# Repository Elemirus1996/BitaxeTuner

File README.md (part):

<p align="center"></p>

<p align="center">
  <a href="https://github.com/Elemirus1996/BitaxeTuner/releases/latest"><b>⬇ Herunterladen</b></a> ·
  <a href="https://elemirus1996.github.io/BitaxeTuner/"><b>Webseite</b></a> ·
  <a href="https://elemirus1996.github.io/BitaxeTuner/pico-luefter/">Pico-Bauanleitung</a> ·
  <a href="#247-betrieb">24/7-Server</a> ·
  <a href="README.en.md"><b>English</b></a>
</p>

# BitaxeTuner

**Automatisches Übertakten, Benchmarken und Überwachen für Bitaxe- und NerdAxe-Miner – als Windows-Programm (WPF)
und als [24/7-Server](#247-betrieb) für Raspberry Pi, Windows oder Docker mit Browser-Oberfläche.**
*Automatic overclocking & benchmarking for Bitaxe and NerdAxe miners – [English README](README.en.md).*

BitaxeTuner erhöht Frequenz und Kernspannung deines Miners Schritt für Schritt, misst jede Kombination
(Hashrate, Leistung, Effizienz, Temperaturen, Fehlerrate) und zeigt dir am Ende die beste Einstellung –
wahlweise für **maximale Hashrate**, **beste Effizienz (J/TH)** oder einen **Kompromiss** aus beidem.
Mehrere Geräte lassen sich **parallel** testen.

> ⚠️ **Übertakten auf eigenes Risiko.** Höhere Frequenz und Spannung erhöhen Leistungsaufnahme und Temperatur
> und können die Hardware beschädigen. Prüfe, ob Netzteil und Kühlung ausreichen.

## Sprache

Desktop-App, Browser-Oberfläche, Push-Meldungen, Tagesbericht, E-Paper-Anzeige und Home Assistant gibt es auf
**Deutsch, Englisch, Spanisch, Portugiesisch (Brasilien), Französisch und Niederländisch** (ab 0.9.12; die vier
neuen Sprachen sind maschinell übersetzt – Verbesserungen von Muttersprachlern gern als Issue oder Pull Request):

- **Desktop-App**: *Einstellungen → Sprache* (Automatisch = Windows-Sprache), wirkt nach einem Neustart der App.
- **Browser**: Sprachauswahl im Kopf (DE, EN, ES, PT, FR, NL) – jeder Browser merkt sich seine Wahl (Standard: Browser-Sprache).
- **Server** (Push, Tagesbericht, E-Paper, Statustexte): *Einstellungen → Sprache des Servers* in der Browser-Oberfläche.
  Ein Raspberry Pi steht ab Werk auf Englisch – für deutsche Meldungen dort „Deutsch“ wählen.
- Zahlen und Datum folgen dem Format des Systems, solange dessen Sprache passt.

## Funktionen

### Tuning

- **Automatischer Benchmark** pro Gerät:
  stabil → Frequenz erhöhen · instabil → Spannung erhöhen · Grenze erreicht → sofort abbrechen.
  Optional wird pro Frequenz auch die niedrigste stabile Spannung gesucht (effizienter).
- **Sicherheits-Watchdog** bei jedem Messwert: max. Chip-Temperatur, VR-Temperatur, Leistung,
  Eingangsspannung, Überhitzungs- und Spannungsfehler der Firmware. Bei Abbruch, Fehler oder Programmende
  werden die ursprünglichen (oder die beste gefundene) Einstellungen wiederhergestellt.
- **Parallelbetrieb** mehrerer Miner, **Pause/Fortsetzen** und Fortsetzen abgebrochener Läufe.
- **Live-Ansicht** mit Hashrate-/Temperaturverlauf, **Heatmap** Frequenz × Spannung, Ergebnistabelle, CSV-Export.
  Ergebnisse per Klick auf die Spalten sortieren (z. B. J/TH aufsteigend) und direkt **in der Automatik speichern**
  (als Voreinstellung für Zeitplan und Strompreis – am Miner ändert sich dabei nichts).
- **Dauertest** und **Effizienz-Ratgeber** (siehe [Bedienung](#automatik-dauertest-vergleich-handy-ansicht)).
- **Simulationsmodus**: Adresse `sim` oder `sim:<profil-id>` eingeben (z. B. `sim:nerdqaxe-plusplus`) –
  zum Ausprobieren ohne echte Hardware (läuft 30× schneller).

### Überwachung

- **Gesamt- und Einzelansicht** mit 14 Kacheln, Wallet-Guthaben (mempool.space / Blockchair), Verlauf 1 h / 24 h /
  7 / 30 Tage aus `history.db` (Hashrate, Temperatur, Leistung, Effizienz J/TH).
- **Netzwerk**: zuletzt gefundene Blöcke, Pool-Ranking, Solo-Chancen BTC/BCH.
- **Gesundheits-Frühwarnung**: täglicher Vergleich der letzten 7 Tage mit den 4 Wochen davor – Kühlung (Temperatur je
  Watt), Effizienz ohne Tuning-Änderung, Lüfter-Drehzahl, abgelehnte Shares, Verfügbarkeit.
- **Watchdog** (Neustart bei 0 Hashrate; ab 0.9.12 auch, wenn die Hashrate eine einstellbare Zeit lang deutlich unter dem
  Normalwert liegt – Einstellungen → Überwachung), **Firmware-Check**, **Best-Diff-Rekorde**, **Tray**, Autostart.
- **Steuer** (nach deutschem Steuerrecht, § 23 EStG): Zuflüsse mit EUR-Kurs, Verkäufe/Haltefrist (FIFO), CSV-Export,
  Stromkosten je Monat neben den Zuflüssen. Mit dem **Pool-Konto** (Mining-Dutch) auch DGB, NMC und andere Coins.

### Neu in 0.9.25

- **Neue IP-Adresse erkennen**: offline gegangene Miner werden per MAC-Adresse im Heimnetz wiedergefunden, die neue
  Adresse wird nach Rückfrage übernommen – Verlauf und Zuordnungen bleiben erhalten.
- **Dein Mining-Jahr**: Rückblick auf 12 Monate oder ein Kalenderjahr, als Seite zum Teilen, im Desktop-Bericht und aufs E-Paper.
- **Mini-Anzeige** in der Desktop-App: kleines Fenster immer im Vordergrund, dazu ein aussagekräftiger Tray-Tooltip.
- **Nachtmodus für den Kiosk**: nachts dimmen oder nur eine große Uhr zeigen.
- **Vergleich mit der Community**: freiwillig und anonym Benchmark-Ergebnisse teilen und sehen, wie der eigene Miner abschneidet.
- **Steuern per Chat**: Neustart, Voreinstellung, Wartungsmodus, Pause und Sicherung aus Discord oder Telegram – nur für
  freigegebene Nutzer, immer mit Rückfrage und Protokoll.
- **Firmware-Update für alle Miner**: einer nach dem anderen, nur offizielle ESP-Miner- und NerdQAxe-Releases (Beta je Miner
  wählbar), vorher gesichert, Dateien geprüft, danach Version, Hashrate und Einstellungen kontrolliert.
- **Saisonaler Feinschliff**: wird es dauerhaft wärmer oder kühler, schlägt BitaxeTuner eine geprüfte Einstellung vor –
  angewendet nur nach Bestätigung.

### Neu in 0.9.24

- **Ausfall einzelner Chips** bei Mehrchip-Minern erkennen (Hashrate je Chip, Meldung nach 30 Minuten, nur lesend).
- **WLAN-Qualität** je Miner: Balken auf der Karte, Verlauf, Warnung bei schwachem oder unruhigem Signal.
- **Pool-Latenz**: Verbindungsaufbau zu jedem Pool alle 10 Minuten gemessen, Spalte „Verbindung“ im Pool-Vergleich.
- **„Rückgängig“** 10 Sekunden lang nach dem Speichern der Einstellungen (Browser und Desktop).
- **Schnellsuche mit Strg+K** für Miner, Seiten, Einstellungen und Aktionen; Desktop zusätzlich F1 und Strg+,.
- **Besser lesbar**: Kontraste nach WCAG AA, „Hoher Kontrast“, größere Schrift, Namen für Screenreader.
- **Mehrere Server in einer Desktop-App**: umschalten und „Alle Server“ mit Summen.
- Pi-5-Gehäuselüfter wieder steuerbar (einmal „Systemdateien per SSH erneuern“), klarere Offline-Meldung,
  Desktop-Einstellungen in Browser-Reihenfolge, Anschlussplan der Lüfterplatine.

### Neu in 0.9.23

- **„Was ist los?“** auf der Miner-Karte: Ursache, was zu prüfen ist, Knopf zur passenden Stelle (Browser und Desktop).
- **Rollen**: Ansicht-Zugänge, die **bedienen** dürfen – Motor pausieren, Voreinstellung anwenden, Neustart, Wartungsmodus,
  optional je Gruppe; Frequenz/Spannung frei, Einstellungen und Steuer bleiben beim Admin.
- **Verschlüsselte Sicherung ins Netz**: WebDAV (Nextcloud, Synology) oder S3 (Backblaze B2, MinIO), AES-256-GCM mit eigenem
  Passwort, nach dem Hochladen geprüft, aus der Liste einspielbar.
- **Pico-Übersicht**: welcher Pico ist wo, Blinken, Neustart, Programm und Schlüssel über WLAN; neu koppeln per
  BOOTSEL-Taste mit Code zum Vergleichen (Pico-Programm 8.5).
- **Chat-Bots**: Discord mit farbigen Karten, Minernamen-Vorschlägen, Bot-Status und privaten Antworten; Warnungen mit
  Knöpfen [Details] [Verlauf] in Discord und Telegram.
- **Übersicht-Vorlagen** (Kompakt, Ertrag, Technik, Wand-Tablet), **Suchfeld in den Einstellungen**, **„?“ an
  Fachbegriffen**, **Hinweise statt leerer Seiten**, **Wischen zwischen Minern** auf dem Handy.

### Neu in 0.9.22

- **Fehlerbehebung SSH nach Pi-Tausch**: Die Desktop-App erkennt einen geänderten SSH-Schlüssel des Servers (neuer Pi unter
  derselben Adresse), zeigt alten und neuen Fingerabdruck und übernimmt den neuen nach Bestätigung; „Schlüssel übertragen“
  prüft zuerst, ob der Schlüssel schon eingetragen ist.

### Neu in 0.9.21

- **Chat-Bots für Telegram und Discord**: /status, /miner, /history, /pool, /system … mit Bild der E-Paper-Seite, nur lesend;
  für Discord ist BitaxeTuner selbst die Bot-Vorlage. Optional angepinnte Live-Nachricht.
- **Ruhezeit**: nachts Push-Meldungen sammeln (Wichtiges sofort), Zusatz- und Server-Lüfter begrenzen.
- **PV-Prognose** (Open-Meteo) für die PV-Automatik und neue Automatik-Art **Heizung** (Raumtemperatur regelt).
- **Amortisation je Miner** mit Garantie-Erinnerung und Abschnitt im Monatsbericht.
- **HTTPS-Assistent** („Verbindung prüfen“, DNS-Rebind-Hinweis) und Zugriff von unterwegs per VPN.
- **Kurse ausblenden**; **Neuigkeiten in allen sechs Sprachen**.

### Neu in 0.9.20

- **Raspberry Pi 5 – Server-Lüfter**: Drehzahl und Stufe sehen und regeln (Firmware, CPU-Kurve oder nach Miner-Temperatur);
  ein stehender Lüfter erscheint im Systemzustand, auch auf dem E-Paper.
- **Weitere Pool-Konten**: public-pool.io, solo.ckpool.org, OCEAN, Braiins Pool und ViaBTC – mit Übersicht-Panel,
  E-Paper-Seite „Pool“, Zuflüssen für die Steuer und Push bei Auszahlungen.
- **Eigene Meilensteine** in den Neuigkeiten (Rekord, erste Auszahlung, Betriebsjahre, kWh, erster Monat im Plus).
- **Neuer Server**: Sicherung gleich beim Einrichten einspielen; Umzug vom alten auf den neuen Server in der Desktop-App.
- **Pi besser geschützt**: Bilder werden vorab verkleinert und speicherbegrenzt verarbeitet, Hardware-Watchdog,
  Speichergrenze für den Dienst, Protokoll übersteht Abstürze, Schreiblast der Speicherkarte im Systemzustand.

### Neu in 0.9.19

- **Spectra 6**: Das große Bild kommt jetzt sicher an, und die Lüfter drehen während der Übertragung nicht mehr kurz auf
  100 % (Pico-Programm 8.4, wird automatisch aufgespielt).

### Neu in 0.9.18

- **Pico-WLAN vom Server**: Beim Einrichten eines Pico übernimmt der Raspberry Pi sein eigenes WLAN – kein Eintippen
  mehr; das Passwort geht direkt zum Pico (bestehende Pis: Systemdateien einmal erneuern).
- **Pico neu einrichten** für eine andere Anzeige löst die alte Zuordnung – kein „Schlüssel passt nicht“ mehr.

### Neu in 0.9.17

- **PV-Automatik**: viel Sonne → volle Leistung, wenig Sonne → Stromsparen. PV-Leistung aus einer Messsteckdose
  (Shelly, Tasmota, FRITZ!DECT) oder aus Home Assistant – darüber auch Anker Solix (Einstellungen → *PV-Anlage*).
- **Effizienz-Ratgeber** mit dem Ziel *Stromsparen* (geringste stabile Leistung).
- **Andere Firmware** (z. B. ZyberOS): in der Übersicht mit allen Werten, nur ohne Benchmark und Übertaktung.
- **Pool-Vorlage nach Zeitplan**: je Zeitfenster eine beliebige Pool-Vorlage, z. B. Mining-Party am Samstagabend.
- **E-Paper in Farbe**: Waveshare 7,3″ Spectra 6 (sechs Farben) als wählbarer Display-Typ, Anschluss an denselben Pins
  der Lüfterplatine (Pico-Programm 8.3).

### Neu in 0.9.16

- **Systemzustand mit Warnung** (Einstellungen → *System*): freier Speicher, Temp-Ordner, Sicherung, USB-Stick, auf dem
  Raspberry Pi Arbeitsspeicher, CPU-Temperatur, Unterspannung und schreibgeschützte Speicherkarte, dazu Uhrzeit (NTP),
  gehäufte Neustarts, Zertifikat und abgebrochene Updates – alle 10 Minuten geprüft, Probleme per Push (Wartung).
- **Server-Update läuft auf dem Server zu Ende**: Sicherung, Download, Installation und Neustart brauchen den Browser
  nicht mehr – die Seite darf geschlossen werden. Notfalls installiert die Desktop-App das signierte Paket **per SSH**
  (mit Handsicherung) und richtet die Systemdateien (Dienst, USB-Regel, Neustart) neu ein.
- **Verlauf wird kleiner**: `history.db` wird einmal kompakt neu geschrieben (geprüft, erst dann getauscht), danach gibt
  das Aufräumen leeren Platz laufend zurück.
- **Pool-Kontrolle**: Meldung, wenn ein Miner von der übertragenen Pool-Vorlage abweicht („wieder angleichen“), und
  Coinbase-Prüfung – zahlt der Pool einen gefundenen Block wirklich an deine Adresse?
- **Wartungs-Erinnerungen** je Miner (Betriebsstunden; Staub/Kühlkörper, Lüfter, Wärmeleitpaste).
- **Kurse**: geschürfte Coins, Merged-Mining-Coins aus dem Pool-Konto und eigene Wunsch-Coins (z. B. ETH, LTC).
- **E-Paper**: neue Seiten *Eigenes Bild*, *Ertrag & Strom*, *Solo-Chance*, *Systemzustand*, *Bitcoin-Netz*, *Pool*,
  *Monatsvergleich*; Regeln je Sonderanzeige und Seitenfolge nach Tageszeit.
- **Neuigkeiten**: Halving-Countdown und Meldung bei großen Kursbewegungen.
- **Wunsch einreichen** direkt in der App – ohne Konto; landet als Idee auf dem Projekt-Board.

### Strom und Kosten

- **Stromtarif** brutto oder netto (mit MwSt.-Satz); optional **Stundenpreise** von aWATTar (Börsenpreis + Aufschlag)
  oder Tibber (Endpreis).
- **Smart Plugs** (Shelly Gen1, Plus/Pro/Gen3, Tasmota und FRITZ!DECT über die FRITZ!Box – jeweils mit Leistungsmessung):
  echter Verbrauch an der Steckdose inklusive
  Netzteil und Zusatzlüftern, Verlauf gegen AxeOS, Meldung bei Ausfall oder steigendem Mehrverbrauch. Es wird nur
  gemessen, **nie geschaltet**.
- **Monats- und Jahresbericht**: Verfügbarkeit, Ø Hashrate/Temperatur/Leistung, J/TH, kWh, Stromkosten und Zuflüsse –
  als CSV oder druckbare Seite (PDF), optional Monats-Push.
- **Ertrag gegen Stromkosten** (ab 0.9.14): Kachel „Gewinn (24 h)“ und Panel mit 24 h, 7 und 30 Tagen und dem laufenden
  Monat, Zeile im Tagesbericht, Saldo im Monatsbericht. Mit Pool-Konto zählen die Gutschriften beim Pool (aktueller Kurs –
  eine Schätzung), sonst die dokumentierten Zuflüsse der Steuer.

### Mehrere Miner

- **Automatische Geräteerkennung** (Netzwerkscan in Desktop und Browser) und passende **Geräteprofile** mit sinnvollen Grenzen.
- **Einstellungen übertragen**: Pool/Fallback und Lüfter eines Miners auf andere übernehmen – Vorschau alt → neu,
  vorher Sicherung je Miner, Worker-Name bleibt, Frequenz und Spannung werden nie übertragen. Ab 0.9.14 auch bei AxeOS ab
  2.15 (z. B. Gamma), das Pools nur noch über seine Pool-Liste annimmt.
- **Pool-Steuerung** (ab 0.9.14, Browser *Pools*, Desktop *Pool-Steuerung …*): Pools einmal als Vorlage eintragen
  (Adresse, Wallet bzw. Konto, Worker-Name, Passwort, TLS) oder aus einem Miner übernehmen und dann auf einzelne oder alle
  Miner als Haupt- bzw. Ersatz-Pool übertragen – Vorschau alt → neu, vorher Sicherung, danach Neustart, alles im
  Protokoll. Worker-Name wahlweise vom Miner behalten, Minername oder genau wie in der Vorlage; Passwörter liegen in
  `secrets.json`.
- **Pool-Vergleich** (ab 0.9.15, gleiche Seite bzw. gleiches Fenster): alle 10 Minuten je Miner gesammelt – je Pool
  abgelehnte Shares, Antwortzeit, Erreichbarkeit als Haupt-Pool, Ausfallzeit, Einsatz als Ersatz-Pool und mit Pool-Konto
  Ertrag je TH und Tag; 24 Stunden, 7 oder 30 Tage.
- **Mining-Art-Vergleich** (ab 0.9.15): Erwartungswert deiner Hashrate bei PPS, PPLNS, Solo BTC und Solo BCH (Difficulty,
  Kurs, Blockprämie + geschätzte Gebühren, Pool-Gebühren einstellbar) mit Stromkosten und Saldo, für Solo die Chance je
  Monat; mit Pool-Konto daneben der tatsächliche Ertrag der letzten 7 Tage.
- **Speicherplatz** (ab 0.9.15, Einstellungen → *Sicherung*): freier Platz auf dem Datenträger des Servers bzw. PCs,
  Größe von Verlauf, Sicherungen und vorherigen Ständen (Kopien beim Einspielen einer Sicherung); Sicherungen und vorherige
  Stände lassen sich nach Bestätigung einzeln löschen (im Protokoll).
- **Ertrags-Automatik** (ab 0.9.15, Gerät → *Automatik* bzw. Gruppen-Automatik, Art *Ertrag*): Liegt der Strompreis über
  dem Break-even-Preis des Miners (Ertrag je TH ÷ Verbrauch je TH), wechselt er auf die sparsame Voreinstellung; volle
  Leistung erst wieder, wenn der Strom um den eingestellten Abstand (Standard 10 %) darunter liegt. Ertrag je TH aus dem
  Pool-Konto, sonst PPS-Erwartung für BTC. Freigabe nötig, jede Änderung im Protokoll.
- **Miner-Gruppen** (z. B. „Community“, „Keller“): Filter und Summen in der Übersicht (Browser), Gruppenfilter im
  Vergleich, Push-Dienste für ganze Gruppen – neue Mitglieder bekommen Meldungen und Berichte automatisch.
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
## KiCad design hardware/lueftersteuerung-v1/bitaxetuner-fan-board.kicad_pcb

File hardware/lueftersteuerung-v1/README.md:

# BitaxeTuner Lüfterplatine v1.0

Fertig bestückbare Platine für die Pico-Lüftersteuerung von BitaxeTuner – derselbe Aufbau wie auf dem Steckbrett
(Anleitung „Pico-Lüftersteuerung“), nur ohne Löten: bei JLCPCB bestellen, Raspberry Pi Pico 2 H aufstecken, fertig.

## Was drauf ist

| Bereich | Inhalt |
|---|---|
| Pico 2 H | steckbar auf zwei Buchsenleisten 1×20 (tauschbar), USB des Pico zum oberen Rand → Raspberry Pi |
| Lüfter K1–K6 | 4-Pin-PWM-Lüfter **5 V** (Molex 47053, mit Nase), je Kanal BC847B + 1 kΩ + 10 kΩ (Ausfallschutz) + 10 kΩ Tacho-Pull-up auf 3,3 V |
| Lüfterstrom | USB-C nur als Stromeingang (5 V von einem USB-Ladegerät, mind. 2 A), Sicherung 2 A, Überspannungsabschaltung ab ca. 6,2 V, TVS-Diode, Elko 470 µF |
| E-Paper | Stiftleiste 1×8: VSYS, GND, DIN, CLK, CS, DC, RST, BUSY (Kabel zum Waveshare Pico-ePaper 7,5" B, dort in die Buchse: VSYS → Pin 39, GND → 38, DIN → 15, CLK → 14, CS → 12, DC → 11, RST → 16, BUSY → 17 – das Modul nicht auf einen Pico stecken) |
| Taster | Stiftleiste 1×8: je Taster Signal + GND nebeneinander (B1 G B2 G B3 G B4 G) |
| Temperaturfühler | 3 Schraubklemmen für DS18B20 (1 = GND, 2 = DQ, 3 = 3,3 V), ein 4,7 kΩ für alle |
| Messpunkte | TP1 Eingang, TP2 +5 V Lüfter, TP3 GND – für die Prüfung mit Labornetzteil |

Größe 115 × 85 mm, 2 Lagen, 4 Befestigungslöcher M3, Massefläche auf beiden Seiten.

Pinbelegung = Firmware `btfan.py` (v6): PWM GP0/2/4/6/8/10, Tacho GP16–21, Taster GP1/3/5/7, DS18B20 GP26,
E-Paper GP11–15 und GP22. Das Skript `skripte/verify.py` prüft die Platine automatisch dagegen.

## Sicherheit (bewusst so gebaut)

- **Ausfallschutz:** Ohne Signal vom Pico (aus, abgestürzt, Kabel ab) sperrt der Transistor über R2 (10 kΩ nach GND)
  und der Lüfter läuft mit voller Drehzahl.
- **Keine 5 V an Pico-Pins:** PWM des Lüfters hängt nur am Transistor, Tacho nur über 10 kΩ an 3,3 V.
- **Lüfterstrom getrennt vom Pico:** Die 5 V vom USB-C gehen nur an die Lüfter, nie an VBUS/VSYS des Pico – sonst
  würde das Ladegerät über den Pico in den Raspberry Pi zurückspeisen. Nur die Masse ist gemeinsam.
- **Falsches Netzteil:** Ab ca. 6,2 V (Streuung 5,8–6,5 V) schalten die zwei MOSFETs ab; ein versehentliches
  12-V-Netzteil erreicht die 5-V-Lüfter nicht. Die Gate-Spannung der MOSFETs ist durch eine 6,2-V-Diode begrenzt.

## Bestellen bei JLCPCB

1. **Gerber hochladen:** `fertigung/bitaxetuner-fan-board-gerber.zip`. Einstellungen: 2 Lagen, 1,6 mm, Farbe nach Wunsch,
   „Remove Order Number“ nach Wunsch. Menge 5 (Mindestmenge).
2. **„PCB Assembly“ einschalten:** Bestückung oben (Top Side), Menge z. B. 2. Wegen der Durchsteckteile (Buchsenleisten,
   Lüfterstecker, Klemmen, USB-C) ist meist **Standard**-Bestückung nötig.
3. **BOM und CPL hochladen:** `fertigung/BOM_JLCPCB.csv` und `fertigung/CPL_JLCPCB.csv`.
4. **Teile prüfen:** Alle 19 Positionen müssen zugeordnet sein. Besonders den Bestand der USB-C-Buchse
   **GCT USB4125-GF-A (C3151650)** prüfen – bei LCSC sind nur wenige auf Lager; falls nötig vorbestellen oder als
   Ersatz eine andere 6-polige USB-C-Buchse **mit durchgesteckten Gehäuselaschen** wählen (Bauform prüfen!).
5. **Bestückungsvorschau genau ansehen** (das ist der wichtigste Schritt):
   - Elko C1: das **+** muss zum Pad mit dem „+“ im Druck zeigen.
   - Dioden D1, D2, D3: der Kathodenstrich zur markierten Seite.
   - Transistoren Q1–Q9 (SOT-23): ein Bein auf der einen, zwei auf der anderen Seite – wie im Druck.
   - USB-C J3: Öffnung zum linken Platinenrand, Kontakte genau auf den Pads, Laschen in den Löchern.
   - Lüfterstecker J11–J16: Pin 1 des Steckers auf dem eckigen Pad.
   Liegt ein Teil verdreht, im Vorschau-Editor drehen – nicht bestellen, solange etwas falsch aussieht.
   Drehungen und Positionen (SOT-23 +180°, Lüfterstecker +180°, Stecker auf Bauteilmitte, Leisten +90°, USB-C
   1,231 mm versetzt) sind in der Datei bereits korrigiert – zuletzt nach der Freigabe der Bestückung durch einen
   JLCPCB-Ingenieur am 04.10.2026. Normalerweise muss in der Vorschau nichts mehr verschoben werden.
6. Kosten (Schätzung vom 03.10.2026): etwa 60–75 € (Economic) bzw. 90–110 € (Standard) für 5 Platinen, davon 2 bestückt,
   inkl. Versand und Einfuhrumsatzsteuer.

## Nach der Lieferung prüfen – vor dem ersten Lüfter

1. **Sichtprüfung:** Lötstellen der Durchsteckteile, keine Brücken, Elko und Dioden richtig herum.
2. **Ohne Pico, ohne Lüfter, mit Labornetzteil** (Strombegrenzung 0,2 A) an **TP1 (+)** und **TP3 (−)**:
   - 5,0 V → an **TP2** ca. 5,0 V.
   - langsam auf 6,5 V erhöhen → TP2 muss auf nahezu 0 V fallen (Abschaltung). Schwelle notieren, sollte zwischen
     5,8 und 6,5 V liegen.
   - zurück auf 5,0 V → TP2 wieder ca. 5,0 V.
   - nie mehr als 15 V anlegen.
3. **USB-Ladegerät an USB-C, einen Lüfter an K1, kein Pico:** Der Lüfter muss sofort mit voller Drehzahl laufen
   (Ausfallschutz ohne Software).
4. **Pico 2 H aufstecken** (USB zum oberen Rand), per USB-Datenkabel an den Raspberry Pi: Der BitaxeTuner-Server
   spielt das Lüfterprogramm auf; unter „Lüfter & Anzeige“ erscheint „Pico verbunden … (Programm v6)“ und die Drehzahl.
5. Ausfallschutz mit Software: bei 30 % das USB-Kabel zum Pi ziehen → nach etwa 5 Sekunden 100 %.

## Dateien

| Datei | Inhalt |
|---|---|
| `bitaxetuner-fan-board.kicad_pcb` / `.kicad_pro` | Platine für KiCad 10 (öffnen, ansehen, 3D-Ansicht, DRC) |
| `fertigung/` | Gerber + Bohrdaten (Zip), Stückliste und Bestückungsliste für JLCPCB, Bestückungsplan als PDF |
| `ansicht-oben.png`, `ansicht-unten.png` | Bilder der Platine |
| `skripte/` | So entsteht die Platine: `build_board.py` (Bauteile, Netze, Platzierung), `to_dsn.py` + Freerouting 1.9 (Leiterbahnen), `finish_board.py` (Masseflächen), `verify.py` (Prüfung gegen Firmware und Sicherheitsregeln), `export_jlc.py` (BOM/CPL), `run.sh` (alles nacheinander) |

## Ehrliche Hinweise

- Die Platine wurde per Skript entworfen und automatisch verlegt; DRC in KiCad 10 ohne Fehler und ohne offene
  Verbindungen, die elektrische Prüfung gegen die Firmware bestanden. **Es gibt keinen separaten Schaltplan
  (.kicad_sch)** – die Schaltung ist in `skripte/build_board.py` (je Bauteil kommentiert) und oben beschrieben.
- Version 1.0 ist ein **Prototyp**: Die erste Bestellung vor dem Dauerbetrieb wie oben beschrieben durchmessen.
- Die Schraubklemmen sitzen am rechten Rand; in welche Richtung ihre Kabeleinführung zeigt, habe ich nicht am
  Datenblatt geprüft – bitte in KiCad (Ansicht → 3D-Betrachter) kontrollieren, bevor bestellt wird.
- Bauteilnummern und Bestände: Stand 03.10.2026 (JLCPCB/LCSC); vor der Bestellung im JLCPCB-Assistenten prüfen.

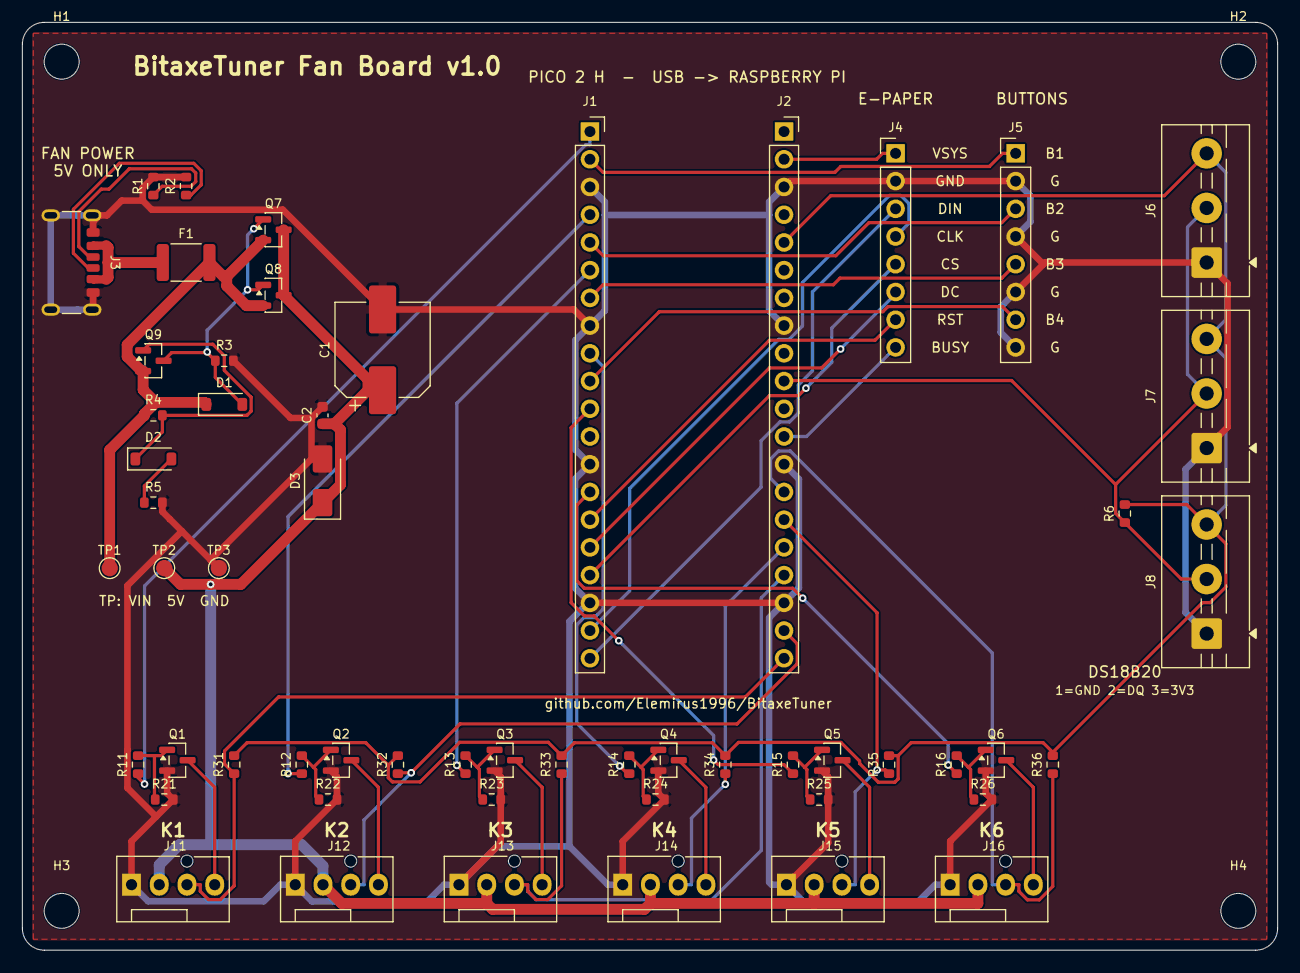
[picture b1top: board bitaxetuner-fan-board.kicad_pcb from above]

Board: 2 copper layers, 115.0 x 85.0 mm, 60 parts (0 on the bottom side), 46 nets.

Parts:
C1: 470uF 25V; CP_Elec_8x10.5
C2: 100nF; C_0603_1608Metric
D1: MM1Z6V2; D_SOD-123
D2: BZT52C5V6; D_SOD-123
D3: SMAJ5.0A; D_SMA
F1: PTC 2A hold; Fuse_1812_4532Metric
H1, H2, H3, H4: M3; MountingHole_3.2mm_M3
J1: Pico 2 H Pins 1-20; PinSocket_1x20_P2.54mm_Vertical
J2: Pico 2 H Pins 40-21; PinSocket_1x20_P2.54mm_Vertical
J3: USB-C 5V FAN POWER; USB_C_Receptacle_GCT_USB4125-xx-x_6P_TopMnt_Horizontal
J4: E-PAPER; PinHeader_1x08_P2.54mm_Vertical
J5: BUTTONS; PinHeader_1x08_P2.54mm_Vertical
J6: DS18B20 #1; TerminalBlock_MaiXu_MX126-5.0-03P_1x03_P5.00mm
J7: DS18B20 #2; TerminalBlock_MaiXu_MX126-5.0-03P_1x03_P5.00mm
J8: DS18B20 #3; TerminalBlock_MaiXu_MX126-5.0-03P_1x03_P5.00mm
J11: Lüfter K1; FanPinHeader_1x04_P2.54mm_Vertical
J12: Lüfter K2; FanPinHeader_1x04_P2.54mm_Vertical
J13: Lüfter K3; FanPinHeader_1x04_P2.54mm_Vertical
J14: Lüfter K4; FanPinHeader_1x04_P2.54mm_Vertical
J15: Lüfter K5; FanPinHeader_1x04_P2.54mm_Vertical
J16: Lüfter K6; FanPinHeader_1x04_P2.54mm_Vertical
Q1, Q2, Q3, Q4, Q5, Q6: BC847B; SOT-23
Q7, Q8: AO3401A; SOT-23
Q9: BC857C; SOT-23
R1, R2: 5.1k; R_0603_1608Metric
R3: 100k; R_0603_1608Metric
R4, R5, R21, R22, R23, R24, R25, R26, R31, R32, R33, R34, R35, R36: 10k; R_0603_1608Metric
R6: 4.7k; R_0603_1608Metric
R11, R12, R13, R14, R15, R16: 1k; R_0603_1608Metric
TP1: VIN; TestPoint_Pad_D1.5mm
TP2: +5V_FAN; TestPoint_Pad_D1.5mm
TP3: GND; TestPoint_Pad_D1.5mm

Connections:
+3V3: J2.5, J6.3, J7.3, J8.3, R6.2, R31.2, R32.2, R33.2, R34.2, R35.2, R36.2
+5V_FAN: C1.1, C2.1, D3.1, J11.2, J12.2, J13.2, J14.2, J15.2, J16.2, Q7.3, Q8.3, TP2.1
BASE1: Q1.1, R11.2, R21.1
BASE2: Q2.1, R12.2, R22.1
BASE3: Q3.1, R13.2, R23.1
BASE4: Q4.1, R14.2, R24.1
BASE5: Q5.1, R15.2, R25.1
BASE6: Q6.1, R16.2, R26.1
BTN1: J1.2, J5.1
BTN2: J1.5, J5.3
BTN3: J1.7, J5.5
BTN4: J1.10, J5.7
CC1: J3.A5, R1.1
CC2: J3.B5, R2.1
EPD_BUSY: J2.12, J4.8
EPD_CLK: J1.19, J4.4
EPD_CS: J1.17, J4.5
EPD_DC: J1.16, J4.6
EPD_DIN: J1.20, J4.3
EPD_RST: J1.15, J4.7
FANPWM1: J11.4, Q1.3
FANPWM2: J12.4, Q2.3
FANPWM3: J13.4, Q3.3
FANPWM4: J14.4, Q4.3
FANPWM5: J15.4, Q5.3
FANPWM6: J16.4, Q6.3
GATE: D1.2, Q7.1, Q8.1, Q9.3, R3.1
GND: C1.2, C2.2, D3.2, J1.3, J1.8, J1.13, J1.18, J2.3, J2.8, J2.13, J2.18, J3.A12, J3.B12, J3.SH, J4.2, J5.2, J5.4, J5.6, J5.8, J6.1, J7.1, J8.1, J11.1, J12.1, J13.1, J14.1, J15.1, J16.1, Q1.2, Q2.2, Q3.2, Q4.2, Q5.2, Q6.2, R1.2, R2.2, R3.2, R5.2, R21.2, R22.2, R23.2, R24.2, R25.2, R26.2, TP3.1
ONEWIRE: J2.10, J6.2, J7.2, J8.2, R6.1
OV_B: D2.1, Q9.1, R4.2
OV_Z: D2.2, R5.1
PWM1: J1.1, R11.1
PWM2: J1.4, R12.1
PWM3: J1.6, R13.1
PWM4: J1.9, R14.1
PWM5: J1.11, R15.1
PWM6: J1.14, R16.1
TACH1: J2.20, J11.3, R31.1
TACH2: J2.19, J12.3, R32.1
TACH3: J2.17, J13.3, R33.1
TACH4: J2.16, J14.3, R34.1
TACH5: J2.15, J15.3, R35.1
TACH6: J2.14, J16.3, R36.1
VIN: F1.1, J3.A9, J3.B9
VIN_F: D1.1, F1.2, Q7.2, Q8.2, Q9.2, R4.1, TP1.1
VSYS: J2.2, J4.1

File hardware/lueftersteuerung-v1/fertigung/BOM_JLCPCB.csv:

Comment,Designator,Footprint,LCSC Part #
Female header 1x20 2.54mm (Pico 2 H),"J1,J2",PinSocket_1x20_P2.54mm_Vertical,C2905423
Molex 47053-1000 fan header 4P,"J11,J12,J13,J14,J15,J16",FanPinHeader_1x04_P2.54mm_Vertical,C240840
1k,"R11,R12,R13,R14,R15,R16",R_0603_1608Metric,C21190
10k,"R21,R31,R22,R32,R23,R33,R24,R34,R25,R35,R26,R36,R4,R5",R_0603_1608Metric,C25804
BC847B,"Q1,Q2,Q3,Q4,Q5,Q6",SOT-23,C20069135
GCT USB4125-GF-A USB-C 6P,J3,USB_C_Receptacle_GCT_USB4125-xx-x_6P_TopMnt_Horizontal,C3151650
5.1k,"R1,R2",R_0603_1608Metric,C23186
PTC 2A hold,F1,Fuse_1812_4532Metric,C960026
AO3401A,"Q7,Q8",SOT-23,C15127
100k,R3,R_0603_1608Metric,C25803
MM1Z6V2,D1,D_SOD-123,C22379464
BC857C,Q9,SOT-23,C20069137
BZT52C5V6,D2,D_SOD-123,C173406
470uF 25V,C1,CP_Elec_8x10.5,C48935394
100nF,C2,C_0603_1608Metric,C14663
SMAJ5.0A,D3,D_SMA,C2925443
Pin header 1x08 2.54mm,"J4,J5",PinHeader_1x08_P2.54mm_Vertical,C32713274
Terminal block 3P 5.0mm,"J6,J7,J8",TerminalBlock_MaiXu_MX126-5.0-03P_1x03_P5.00mm,C5188435
4.7k,R6,R_0603_1608Metric,C23162

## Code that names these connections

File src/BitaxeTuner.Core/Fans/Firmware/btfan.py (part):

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try:
    import onewire
    import ds18x20
    ds = ds18x20.DS18X20(onewire.OneWire(Pin(26)))
except Exception:
    ds = None

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# ---------- e-Paper 7.5" B V2 ----------

epd_spi = None
epd_cs = Pin(EPD_PINS[2], Pin.OUT, value=1)
epd_dc = Pin(EPD_PINS[3], Pin.OUT, value=0)
epd_rst = Pin(EPD_PINS[4], Pin.OUT, value=1)
epd_busy = Pin(EPD_PINS[5], Pin.IN, Pin.PULL_UP)
img = None           # bytearray(2 * PLANE): black plane (1 = white), red plane (1 = red)
img_pos = 0
img_len = 0
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    # BUSY high = idle; UC8179 needs the status command 0x71 first, Spectra 6 reports it directly
    if epd_kind == 0:
        epd_cmd(0x71)
    return epd_busy.value() == 1


def epd_wait(ms):
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        epd_spi = machine.SPI(EPD_SPI, baudrate=4000000, polarity=0, phase=0,
                              sck=Pin(EPD_PINS[1]), mosi=Pin(EPD_PINS[0]), miso=Pin(28))
        # and take DC / RST back as outputs in case a firmware still claimed them for SPI
        epd_dc.init(Pin.OUT, value=0)
        epd_rst.init(Pin.OUT, value=1)


def epd_init():
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

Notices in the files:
README.md:
- **Keine Gewähr.** BitaxeTuner wird ohne jede Garantie bereitgestellt (GPL-3.0, Abschnitte 15–16). Übertakten,
- Beiträge: siehe [CONTRIBUTING.md](CONTRIBUTING.md). Beiträge stehen unter derselben Lizenz (GPL-3.0).
Copyright © 2026 BitaxeTuner contributors. Lizenz: **GNU GPL v3.0** – siehe [LICENSE](LICENSE).
